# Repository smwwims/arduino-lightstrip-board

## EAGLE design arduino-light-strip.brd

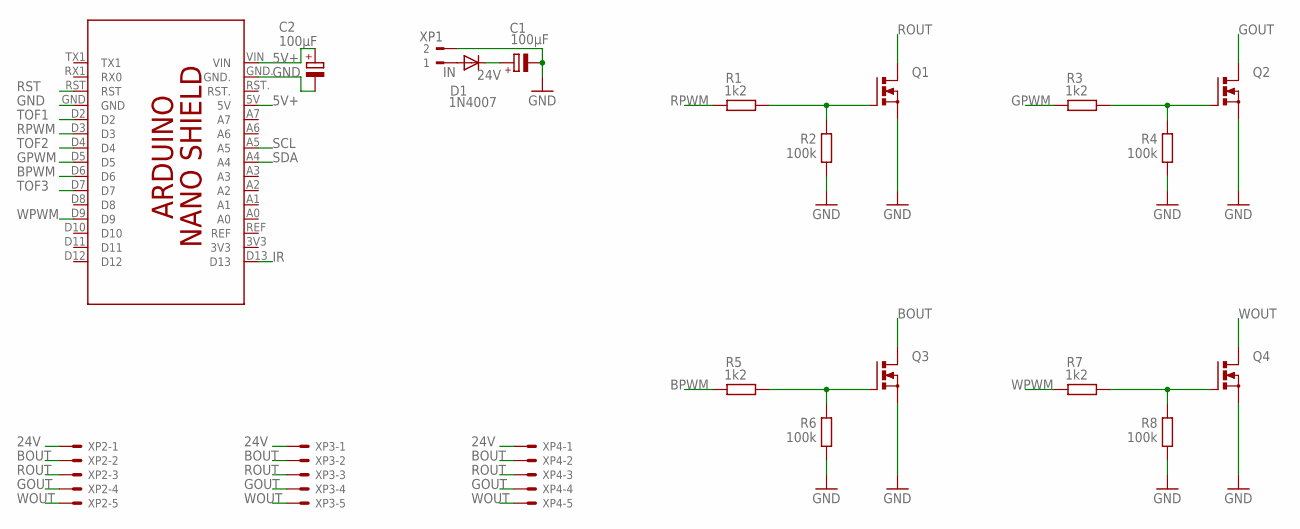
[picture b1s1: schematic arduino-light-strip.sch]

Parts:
C1, C2: 100µF; RCL_E5-6
D1: 1N4007; DIODE_F126-10
PCB1: 0_WSH_FAVORITES_ARDUINO_NANO
Q1, Q2, Q3, Q4: 0_WSH_FAVORITES_BUZ11BV; 0_WSH_FAVORITES_TO220BV
R1, R3, R5, R7: 1k2; R1206
R2, R4, R6, R8: 100k; R1206
XP1: 180-3; CON-WEIDMUELLER-SL35_180-2
XP2, XP3, XP4: 22-27-2051-05; 6410-05

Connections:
5V+: C2.+, PCB1.5V, PCB1.VIN
24V: C1.+, D1.C, XP2.1, XP3.1, XP4.1
BOUT: Q3.D, XP2.2, XP3.2, XP4.2
BPWM: PCB1.D6, R5.2
GND: C1.-, C2.-, PCB1.GND, PCB1.GND., Q1.S, Q2.S, Q3.S, Q4.S, R2.2, R4.2, R6.2, R8.2, XP1.2
GOUT: Q2.D, XP2.4, XP3.4, XP4.4
GPWM: PCB1.D5, R3.2
IN: D1.A, XP1.1
IR: PCB1.D13
unnamed: Q1.G, R1.1, R2.1
unnamed: Q2.G, R3.1, R4.1
unnamed: Q3.G, R5.1, R6.1
unnamed: Q4.G, R7.1, R8.1
ROUT: Q1.D, XP2.3, XP3.3, XP4.3
RPWM: PCB1.D3, R1.2
RST: PCB1.RST
SCL: PCB1.A5
SDA: PCB1.A4
TOF1: PCB1.D2
TOF2: PCB1.D4
TOF3: PCB1.D7
WOUT: Q4.D, XP2.5, XP3.5, XP4.5
WPWM: PCB1.D9, R7.2

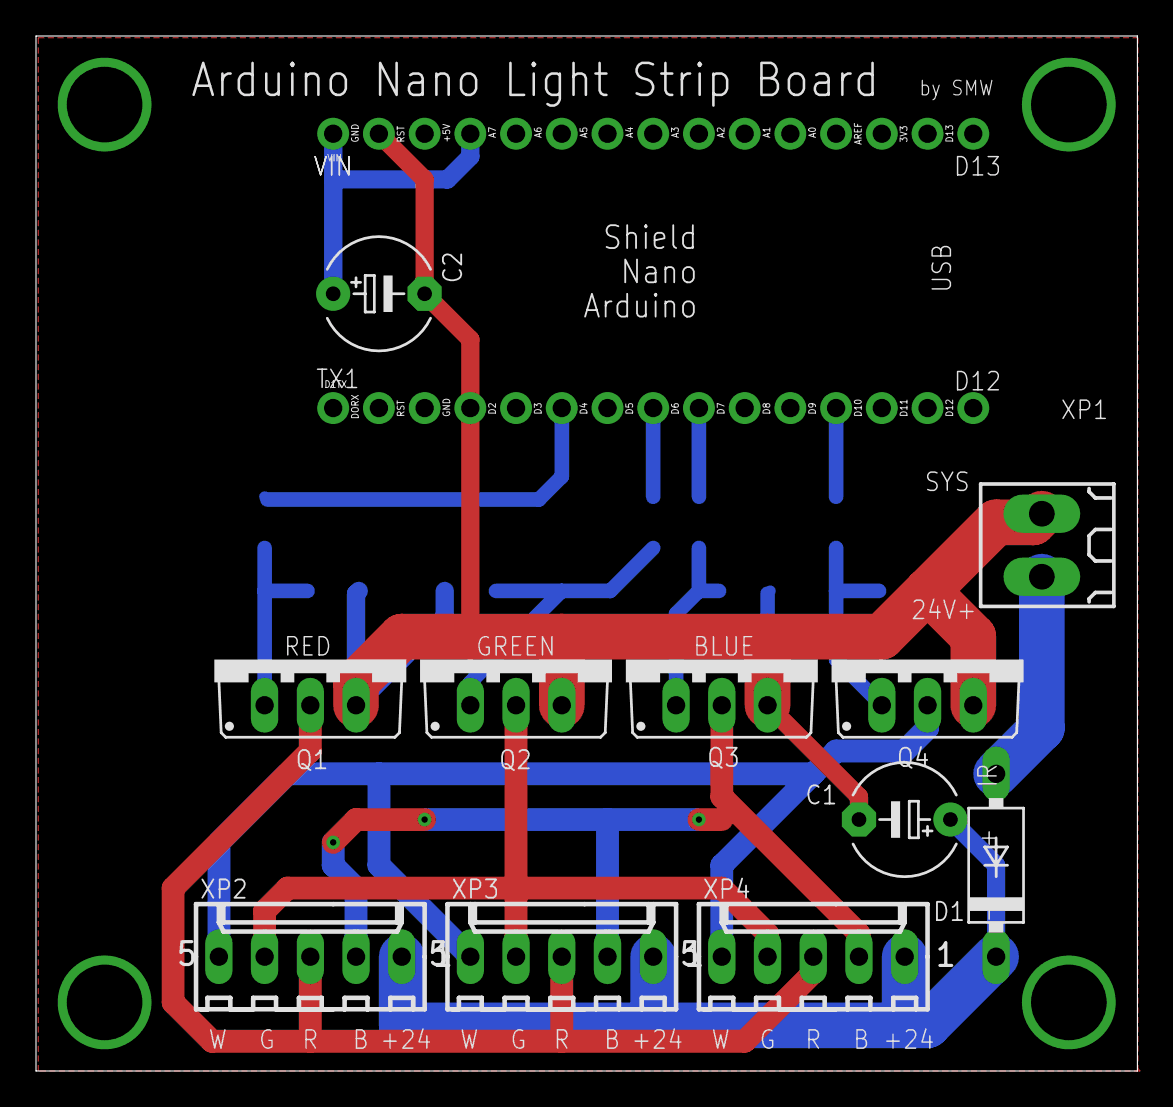
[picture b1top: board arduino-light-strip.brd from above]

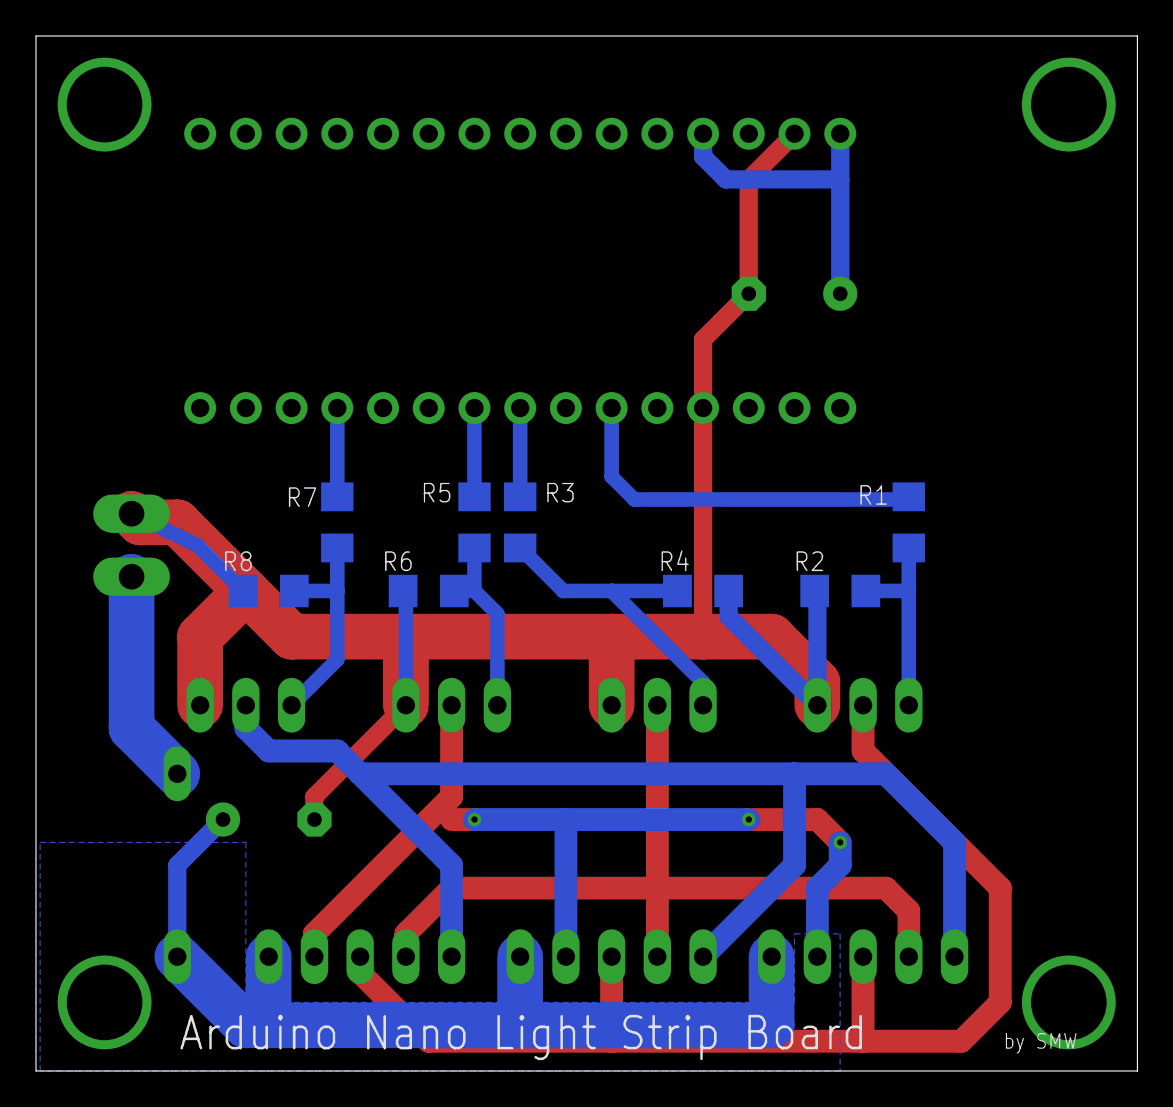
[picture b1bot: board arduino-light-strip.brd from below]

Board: 2 copper layers, 61.2 x 57.5 mm, 20 parts (8 on the bottom side), 16 nets.

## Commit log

2024-06-18 Add schematic v1
2024-06-18 Add PCB Design
2024-06-20 Test Code
